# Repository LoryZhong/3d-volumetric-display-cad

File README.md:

# 3D Volumetric Display — Hardware Design Files

Mechanical CAD and PCB design files for a rotational swept-volume volumetric display based on persistence of vision (POV). Structural components were designed in SolidWorks and fabricated by FDM 3D printing (PLA, with PETG for the motor damper). The custom HUB75E adapter PCB was designed in KiCad.

This repository accompanies the software driver at [LoryVox](https://github.com/LoryZhong/LoryVox).

## Assembly Overview

The mechanical structure is divided into three subsystems:

### Rotate Part — Core Rotating Assembly

The central rotating body that carries all on-rotor electronics. Includes the core (with Raspberry Pi 4 mounting bosses and bearing locators), plug, slip-ring cylinder (sized for the ASL9013 2-line slip ring), bottom bearing ring, GT2 pulley bore, half-disc photo-interrupter flag, and top cover.

- Upper bearing: 6015 deep-groove ball bearing (bore large enough for the Raspberry Pi to pass through during assembly)
- Lower bearing: 6804 deep-groove ball bearing (bore sized for the ASL9013 slip ring)
- Bearings are retained by interference-fit bosses — no adhesive required

**Contents of `rotate-part/`:** Core, plug, slip-ring cylinder, bottom bearing ring, half-disc flag, top cover.

### Frame — LED Panel Mounting Frame

Rectangular frames that hold each HUB75E LED panel (P2.5 64x64) at the correct radial distance from the rotation axis. Carbon-fibre rods (6 mm dia.) connect the frames to the core assembly. Version 2 redesigned the rod socket diameter to 6.1 mm with clearance chamfers, allowing post-print finishing with a 6.1 mm drill bit.

**Contents of `frame/`:** LED panel frame (Version 2), rod socket geometry.

### Support Part — Stationary Base and Motor Mount

The non-rotating platform that houses the power supply, motor, brush holder (AS-PL ABH6004S), and photo-interrupter sensor. Includes the sliding motor-mount bracket for GT2 belt tension adjustment and the PETG motor damper for vibration attenuation.

**Contents of `support-part/`:** Stationary base, motor mount (sliding slot), motor damper (PETG), partial enclosure panels.

### PCB — Custom HUB75E Adapter Board

KiCad project for the 3.3 V-to-5 V level-shifting adapter between the Raspberry Pi 4 GPIO header and two HUB75E LED panel connectors. Uses three 74HCT245 octal bus transceivers (SOIC-20) with per-IC 100 nF decoupling capacitors. Includes a JST-XH 3-pin socket for the photo-interrupter and a JST-XH 2-pin socket for DC-DC power input.

**Contents of `pcb/`:** KiCad project (`.kicad_pro`, `.kicad_sch`, `.kicad_pcb`), BOM (`.csv`), schematic PDF, fabrication Gerbers (`.zip`).

| PCB Parameter | Value |
|---------------|-------|
| Layers | 2 |
| Substrate | FR-4, 0.8 mm |
| Copper | 1 oz |
| Min trace | 0.33 mm |
| Via drill/ring | 0.4/1.1 mm |
| Finish | HASL lead-free |

## Printing Notes

| Parameter | Value |
|-----------|-------|
| Material | PLA (structural parts), PETG (motor damper) |
| Layer height | 0.2 mm |
| Infill | 20–40% (structural), 100% (bearing bosses) |
| Fasteners | M4 hex-socket screws throughout |

## License

MIT

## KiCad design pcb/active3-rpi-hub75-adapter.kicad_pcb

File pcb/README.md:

# Custom HUB75E Adapter PCB

Custom adapter PCB for the 3D volumetric display project, **based on and modified from** the [Active-3 adapter](https://github.com/hzeller/rpi-rgb-led-matrix/tree/master/adapter/active-3) by Henner Zeller (part of the [rpi-rgb-led-matrix](https://github.com/hzeller/rpi-rgb-led-matrix) project).

## What was changed

The original Active-3 design supports up to 3 panel chains with 4x 74HCT245 ICs. This version was modified for the volumetric display rotor:

- Reduced from 3 HUB75 outputs to 2 (matching the dual-panel rotating arm)
- Reduced from 4x to 3x 74HCT245 ICs
- Reworked board outline to fit inside the 3D-printed rotor core
- Added JST-XH 3-pin socket for photo-interrupter connection
- Added JST-XH 2-pin socket for DC-DC 5V power input
- Adjusted trace routing for improved CLK signal integrity (straighter path, increased clearance)
- Corrected via dimensions: drill 0.4 mm / annular ring 1.1 mm
- Minimum trace width: 0.33 mm (widened from original)
- Board thickness: 0.8 mm (thinner than standard 1.6 mm, to reduce rotor weight)

## Files in this directory

| File | Status | Description |
|------|--------|-------------|
| `active3-rpi-hub75-adapter.kicad_pcb` | **Modified** | PCB layout with custom modifications |
| `active3-rpi-hub75-adapter.kicad_sch` | **Modified** | Schematic with custom modifications |
| `active3-rpi-hub75-adapter.kicad_pro` | From original | KiCad project file (may not reflect all changes) |
| `active3-rpi-hub75-adapter.kicad_prl` | From original | KiCad local settings |
| `active3-rpi-hub75-adapter.csv` | From original | BOM (does not reflect modified design) |
| `active3-rpi-hub75-adapter-fab.zip` | From original | Gerbers (does not reflect modified design) |
| `schematic.pdf` | From original | Schematic PDF (does not reflect modified design) |

> **Note:** Only the `.kicad_pcb` and `.kicad_sch` files reflect the actual custom design used in the project. The other files are inherited from the original Active-3 project and may not match the modified board. Refer to the schematic and PCB layout files for the as-built design.

## Original design credit

Based on the Active-3 adapter by [Henner Zeller](https://github.com/hzeller), licensed under the rpi-rgb-led-matrix project. The original design is an open-source KiCad PCB using HCT245 level shifters to interface Raspberry Pi 3.3V GPIO with 5V HUB75 panels.

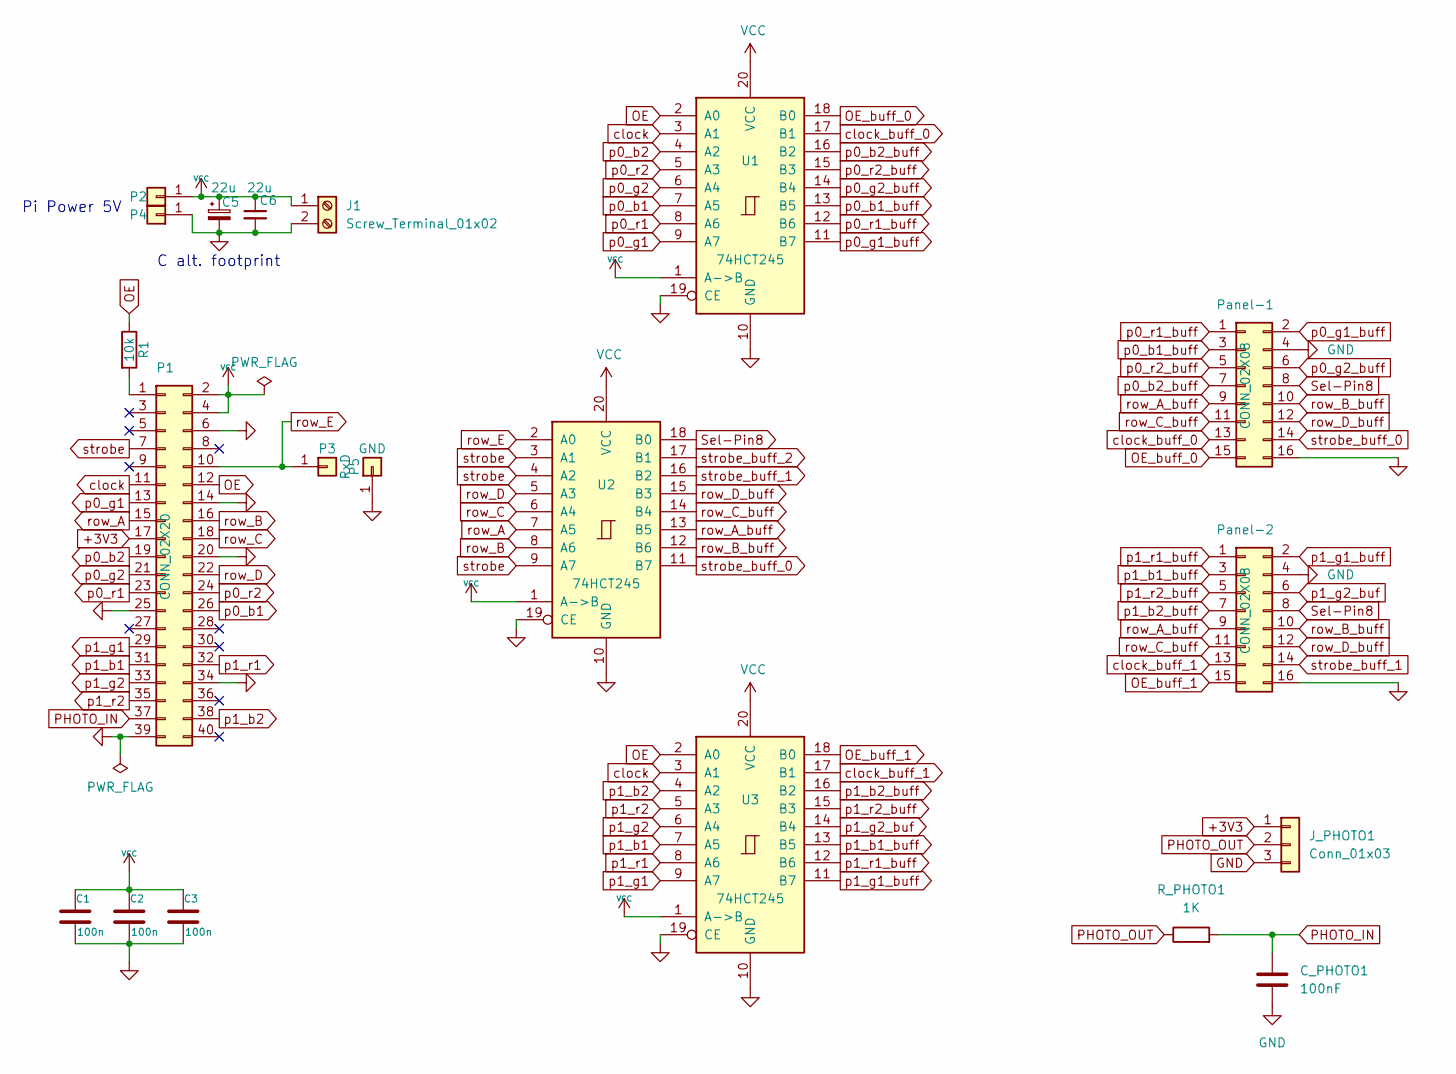
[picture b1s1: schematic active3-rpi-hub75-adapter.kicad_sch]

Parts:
C1, C2, C3: 100n; C_0805_2012Metric
C5: 22u; CP_Radial_D6.3mm_P2.50mm
C6: 22u; C_1206_3216Metric
C_PHOTO1: 100nF; C_0805_2012Metric
J1: Screw_Terminal_01x02
J_PHOTO1: Conn_01x03; JST_XH_B3B-XH-A_1x03_P2.50mm_Vertical
P1: CONN_02X20; Pin_Header_Straight_2x20
P2: +5V; Pin_Header_Straight_1x01
P3: RxD; Pin_Header_Straight_1x01
P4, P5: GND; Pin_Header_Straight_1x01
Panel-1, Panel-2: CONN_02X08; IDC-Header_2x08_P2.54mm_Vertical
R1: 10k; R_0805_2012Metric
R_PHOTO1: 1K; R_0805_2012Metric
U1, U2, U3: 74HCT245; SOIC-20W_7.5x12.8mm_P1.27mm

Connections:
+3V3: J_PHOTO1.1, P1.17
GND: C1.2, C2.2, C3.2, C5.2, C6.2, C_PHOTO1.2, J1.2, J_PHOTO1.3, P1.6, P1.14, P1.20, P1.25, P1.34, P1.39, P4.1, P5.1, Panel-1.4, Panel-1.16, Panel-2.4, Panel-2.16, U1.10 (GND), U1.19 (CE), U2.10 (GND), U2.19 (CE), U3.10 (GND), U3.19 (CE)
unnamed: P1.1, R1.2
OE: P1.12, R1.1, U1.2 (A0), U3.2 (A0)
OE_buff_0: Panel-1.15, U1.18 (B0)
OE_buff_1: Panel-2.15, U3.18 (B0)
PHOTO_IN: C_PHOTO1.1, P1.37, R_PHOTO1.2
PHOTO_OUT: J_PHOTO1.2, R_PHOTO1.1
Sel-Pin8: Panel-1.8, Panel-2.8, U2.18 (B0)
VCC: C1.1, C2.1, C3.1, C5.1, C6.1, J1.1, P1.2, P1.4, P2.1, U1.1 (A->B), U1.20 (VCC), U2.1 (A->B), U2.20 (VCC), U3.1 (A->B), U3.20 (VCC)
clock: P1.11, U1.3 (A1), U3.3 (A1)
clock_buff_0: Panel-1.13, U1.17 (B1)
clock_buff_1: Panel-2.13, U3.17 (B1)
p0_b1: P1.26, U1.7 (A5)
p0_b1_buff: Panel-1.3, U1.13 (B5)
p0_b2: P1.19, U1.4 (A2)
p0_b2_buff: Panel-1.7, U1.16 (B2)
p0_g1: P1.13, U1.9 (A7)
p0_g1_buff: Panel-1.2, U1.11 (B7)
p0_g2: P1.21, U1.6 (A4)
p0_g2_buff: Panel-1.6, U1.14 (B4)
p0_r1: P1.23, U1.8 (A6)
p0_r1_buff: Panel-1.1, U1.12 (B6)
p0_r2: P1.24, U1.5 (A3)
p0_r2_buff: Panel-1.5, U1.15 (B3)
p1_b1: P1.31, U3.7 (A5)
p1_b1_buff: Panel-2.3, U3.13 (B5)
p1_b2: P1.38, U3.4 (A2)
p1_b2_buff: Panel-2.7, U3.16 (B2)
p1_g1: P1.29, U3.9 (A7)
p1_g1_buff: Panel-2.2, U3.11 (B7)
p1_g2: P1.33, U3.6 (A4)
p1_g2_buf: Panel-2.6, U3.14 (B4)
p1_r1: P1.32, U3.8 (A6)
p1_r1_buff: Panel-2.1, U3.12 (B6)
p1_r2: P1.35, U3.5 (A3)
p1_r2_buff: Panel-2.5, U3.15 (B3)
row_A: P1.15, U2.7 (A5)
row_A_buff: Panel-1.9, Panel-2.9, U2.13 (B5)
row_B: P1.16, U2.8 (A6)
row_B_buff: Panel-1.10, Panel-2.10, U2.12 (B6)
row_C: P1.18, U2.6 (A4)
row_C_buff: Panel-1.11, Panel-2.11, U2.14 (B4)
row_D: P1.22, U2.5 (A3)
row_D_buff: Panel-1.12, Panel-2.12, U2.15 (B3)
row_E: P1.10, P3.1, U2.2 (A0)
strobe: P1.7, U2.3 (A1), U2.4 (A2), U2.9 (A7)
strobe_buff_0: Panel-1.14, U2.11 (B7)
strobe_buff_1: Panel-2.14, U2.16 (B2)
strobe_buff_2: U2.17 (B1)

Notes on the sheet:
Pi Power 5V
C alt. footprint

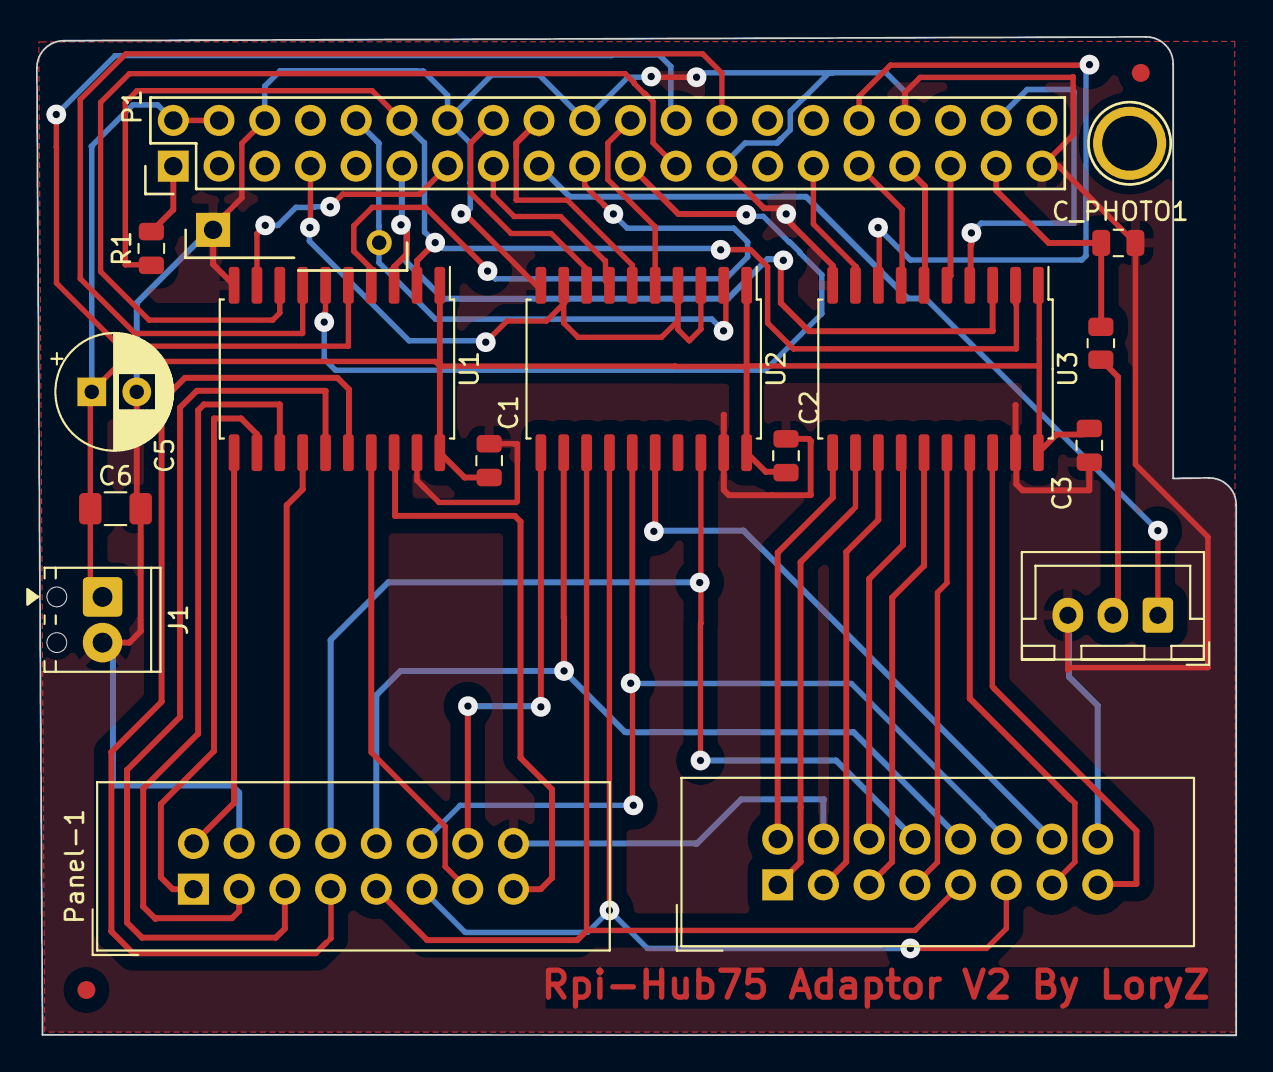
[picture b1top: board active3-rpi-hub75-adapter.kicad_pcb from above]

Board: 2 copper layers, 66.6 x 55.5 mm, 19 parts (0 on the bottom side), 49 nets.

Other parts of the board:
P21: CONN_01X01; 1pin
